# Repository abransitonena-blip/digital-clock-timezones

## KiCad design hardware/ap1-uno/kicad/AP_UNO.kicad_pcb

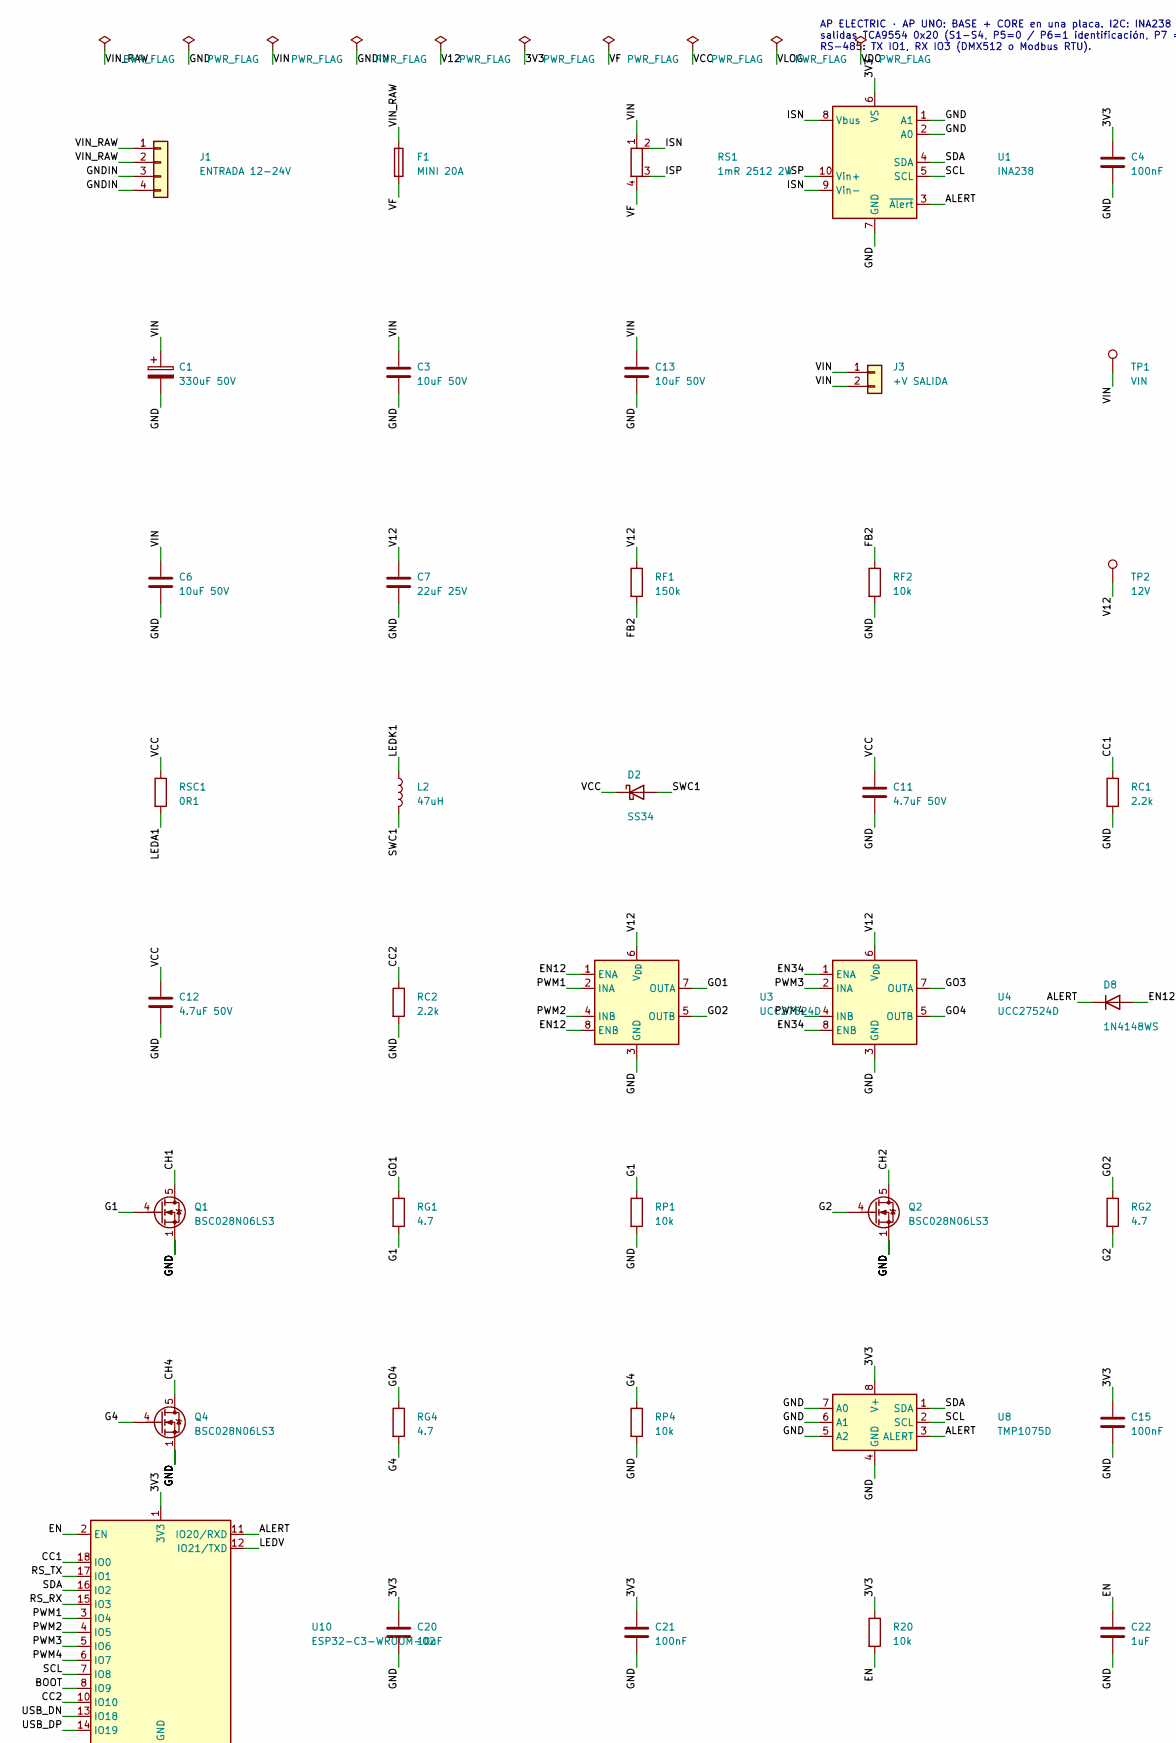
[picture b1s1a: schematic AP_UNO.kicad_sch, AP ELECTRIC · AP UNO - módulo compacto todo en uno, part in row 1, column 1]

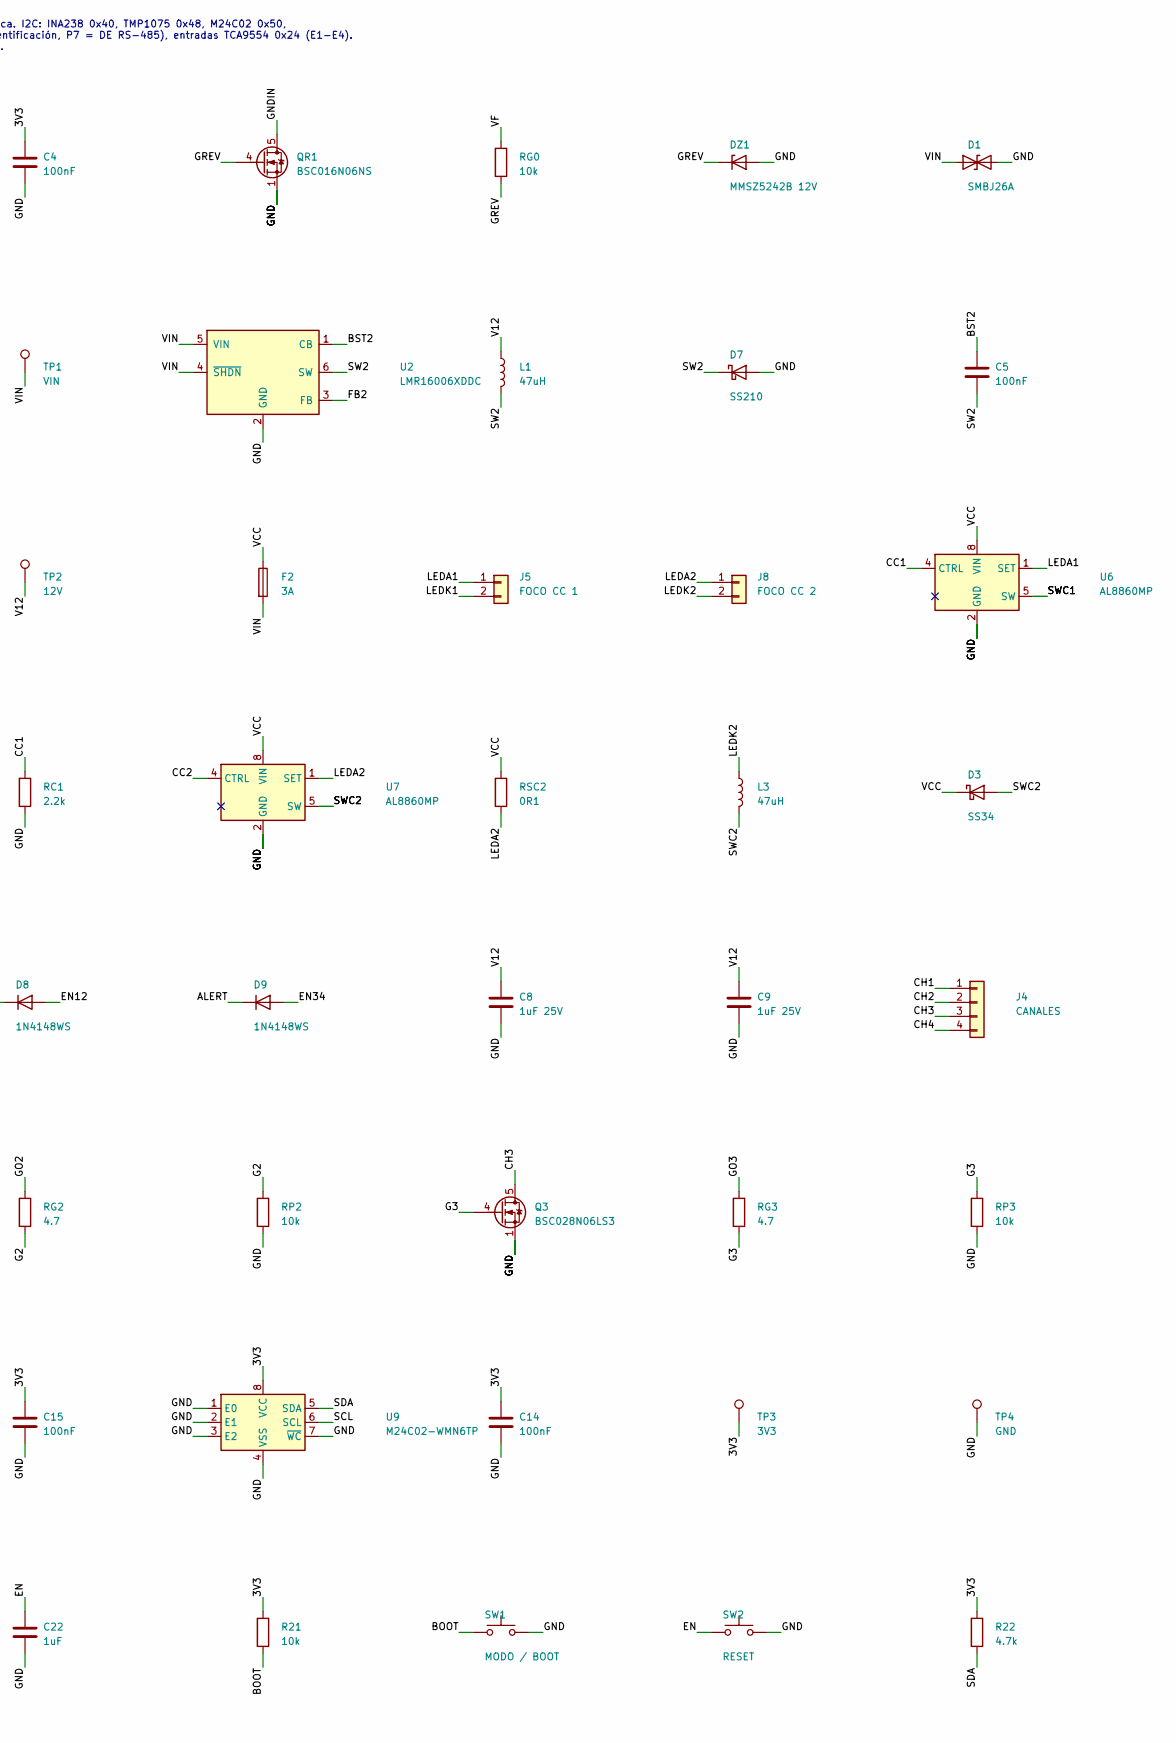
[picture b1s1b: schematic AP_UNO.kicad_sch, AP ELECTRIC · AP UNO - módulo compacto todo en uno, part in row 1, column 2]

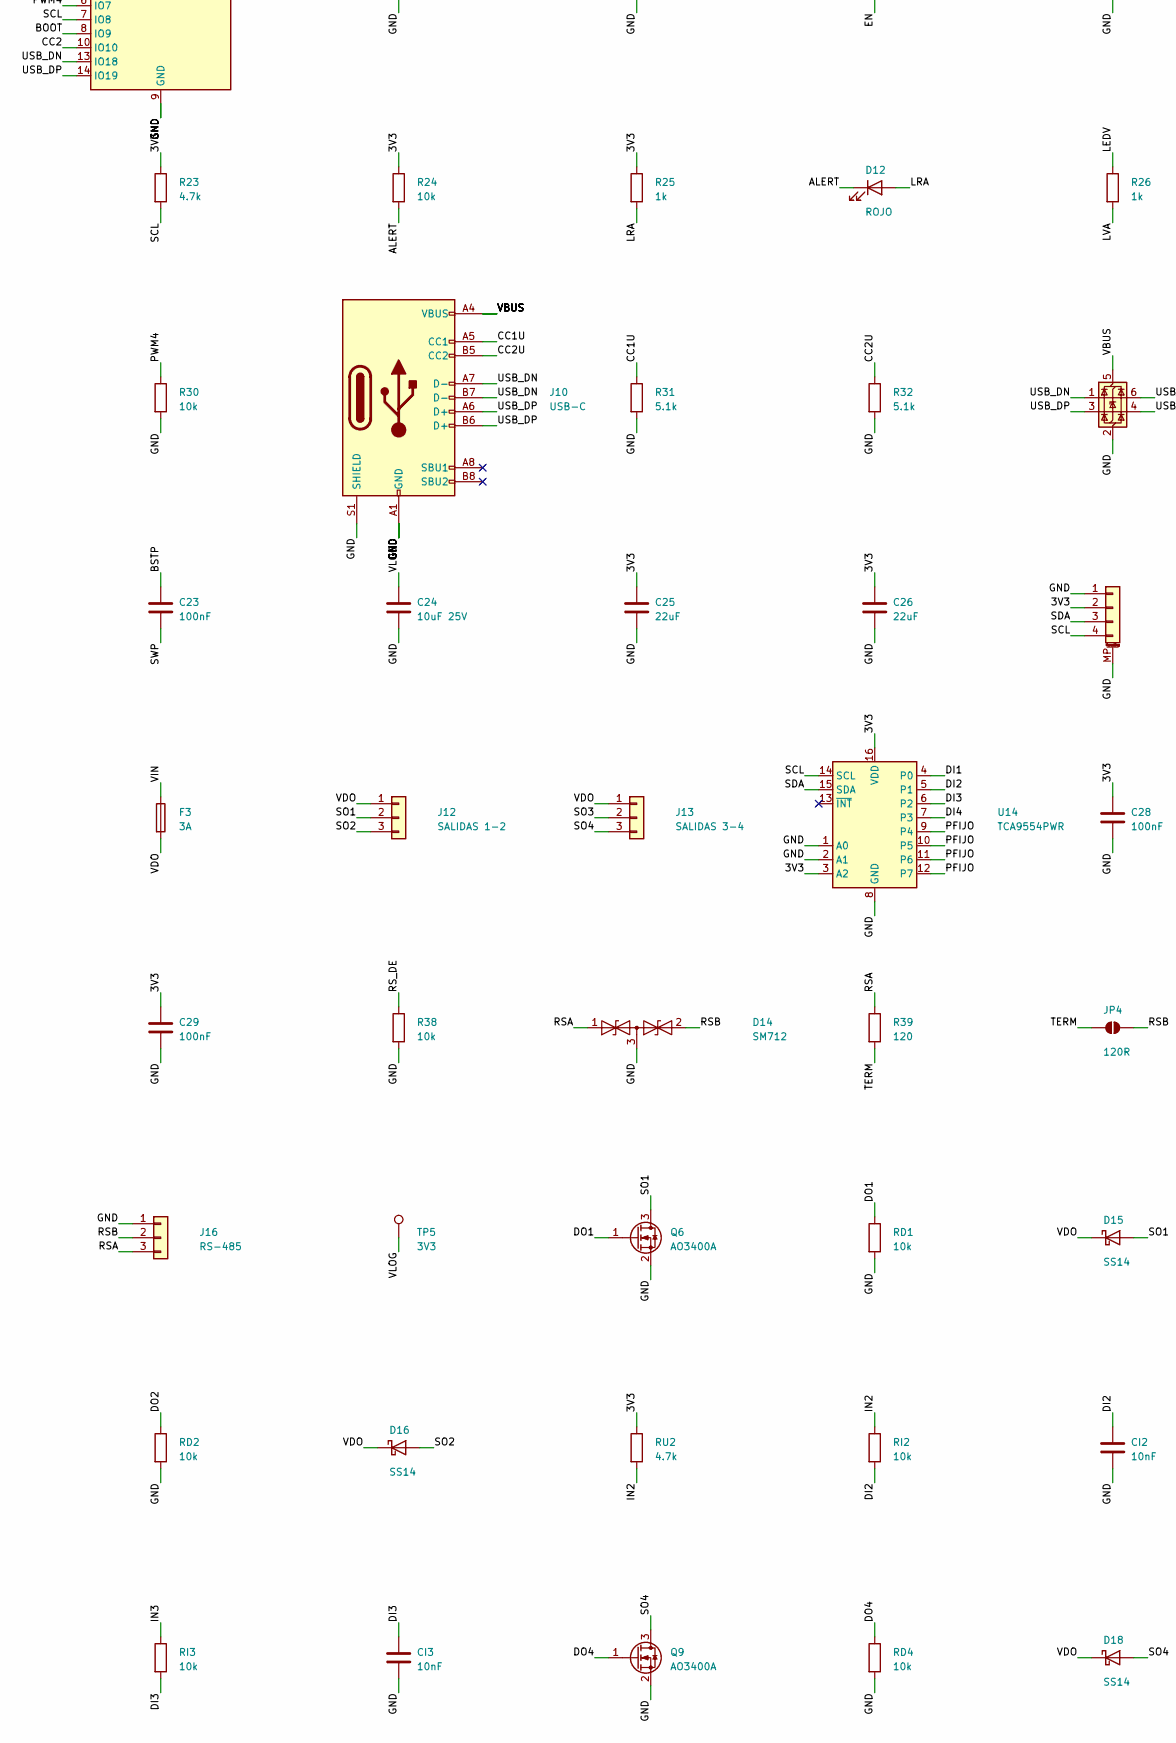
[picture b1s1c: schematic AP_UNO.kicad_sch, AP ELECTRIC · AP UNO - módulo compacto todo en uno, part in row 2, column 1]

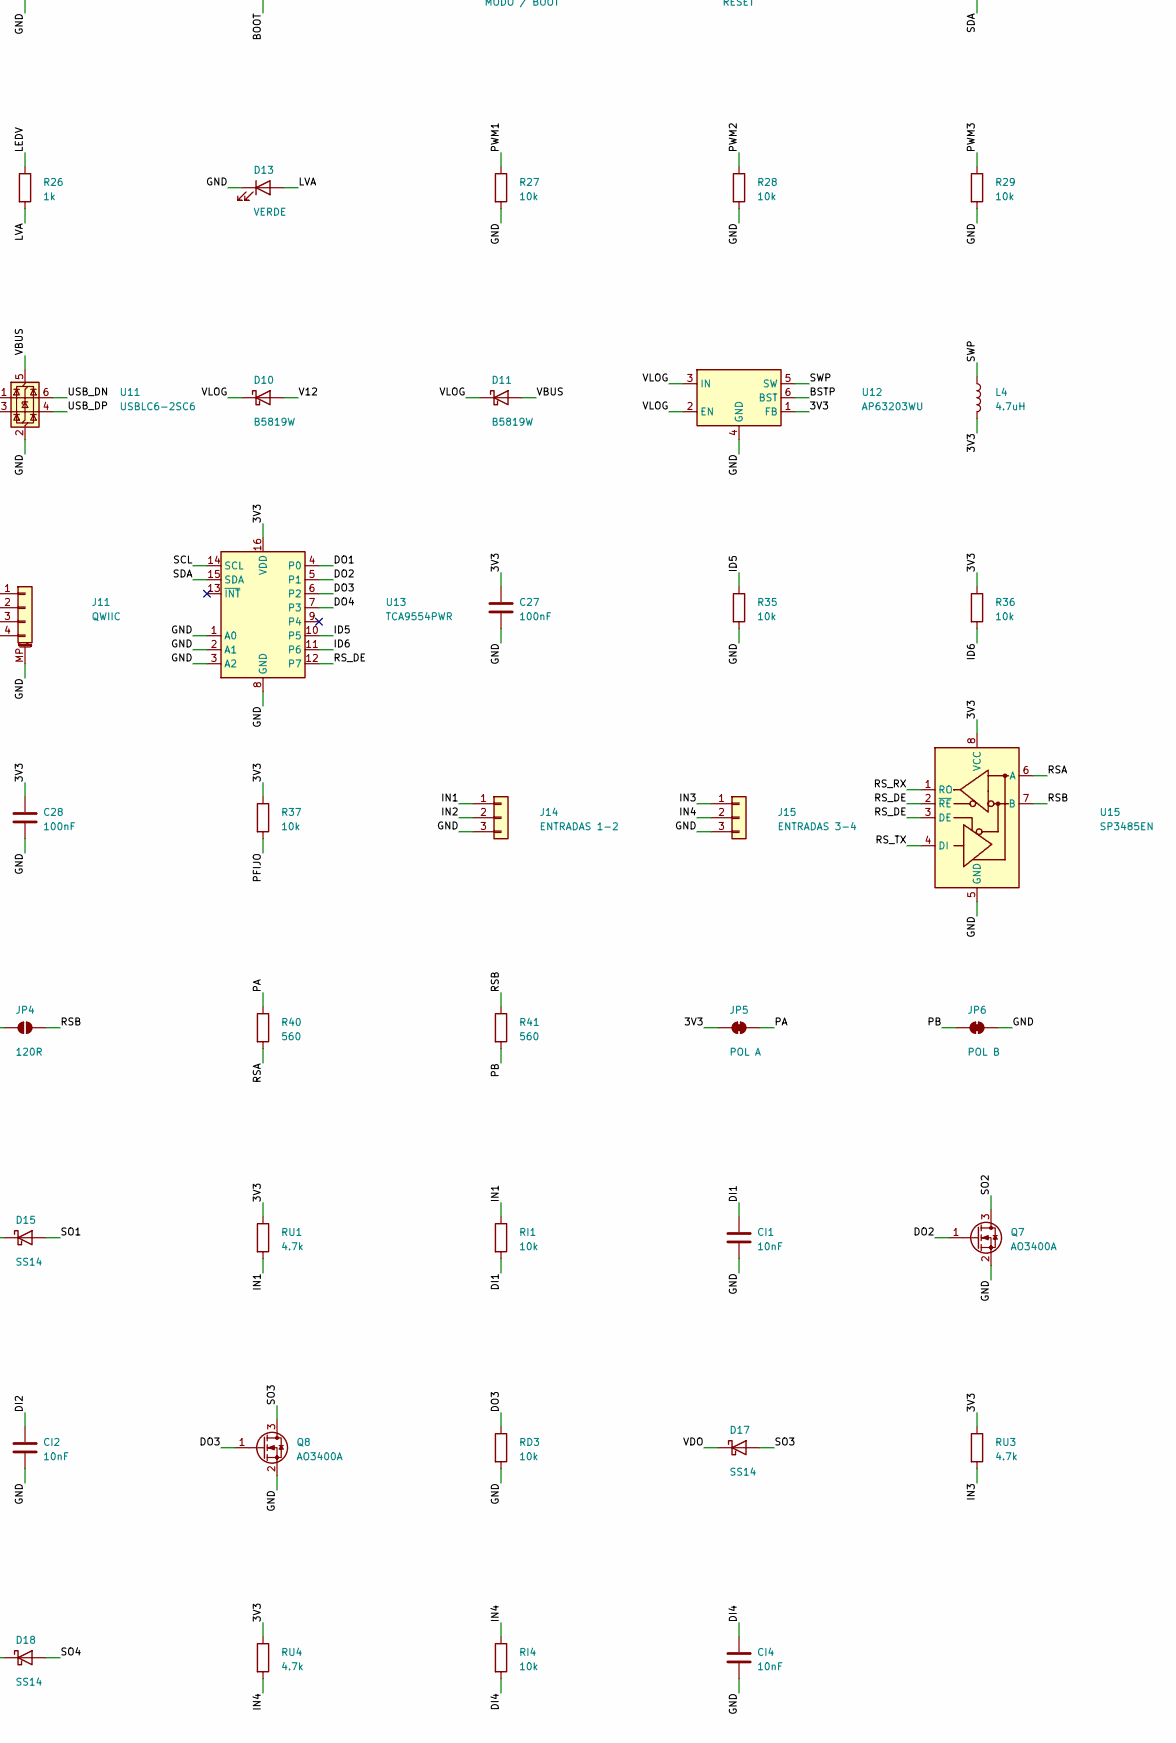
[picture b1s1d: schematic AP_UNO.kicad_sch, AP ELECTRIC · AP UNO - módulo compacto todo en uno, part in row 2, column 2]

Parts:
C1: 330uF 50V; CP_Elec_10x10.5
C3, C6, C13: 10uF 50V; C_1206_3216Metric
C4, C5, C14, C15, C21, C23, C27, C28, C29: 100nF; C_0603_1608Metric
C7: 22uF 25V; C_1206_3216Metric
C8, C9: 1uF 25V; C_0603_1608Metric
C11, C12: 4.7uF 50V; C_1206_3216Metric
C20: 10uF; C_0805_2012Metric
C22: 1uF; C_0603_1608Metric
C24: 10uF 25V; C_1206_3216Metric
C25, C26: 22uF; C_0805_2012Metric
CI1, CI2, CI3, CI4: 10nF; C_0603_1608Metric
D1: SMBJ26A; D_SMB
D2, D3: SS34; D_SMA
D7: SS210; D_SMA
D8, D9: 1N4148WS; D_SOD-323
D10, D11: B5819W; D_SOD-123
D12: ROJO; LED_0603_1608Metric
D13: VERDE; LED_0603_1608Metric
D14: SM712; SOT-23
D15, D16, D17, D18: SS14; D_SMA
DZ1: MMSZ5242B 12V; D_SOD-123
F1: MINI 20A; Fuseholder_Blade_Mini_Keystone_3568
F2, F3: 3A; Fuse_1206_3216Metric
J1: ENTRADA 12-24V; JST_VH_B4P-VH_1x04_P3.96mm_Vertical
J3: +V SALIDA; JST_VH_B2P-VH_1x02_P3.96mm_Vertical
J4: CANALES; JST_VH_B4P-VH_1x04_P3.96mm_Vertical
J5: FOCO CC 1; JST_XH_B2B-XH-A_1x02_P2.50mm_Vertical
J8: FOCO CC 2; JST_XH_B2B-XH-A_1x02_P2.50mm_Vertical
J10: USB-C; USB_C_Receptacle_HRO_TYPE-C-31-M-12
J11: QWIIC; JST_SH_SM04B-SRSS-TB_1x04-1MP_P1.00mm_Horizontal
J12: SALIDAS 1-2; JST_XH_B3B-XH-A_1x03_P2.50mm_Vertical
J13: SALIDAS 3-4; JST_XH_B3B-XH-A_1x03_P2.50mm_Vertical
J14: ENTRADAS 1-2; JST_XH_B3B-XH-A_1x03_P2.50mm_Vertical
J15: ENTRADAS 3-4; JST_XH_B3B-XH-A_1x03_P2.50mm_Vertical
J16: RS-485; JST_XH_B3B-XH-A_1x03_P2.50mm_Vertical
JP4: 120R; SolderJumper-2_P1.3mm_Open_RoundedPad1.0x1.5mm
JP5: POL A; SolderJumper-2_P1.3mm_Bridged_RoundedPad1.0x1.5mm
JP6: POL B; SolderJumper-2_P1.3mm_Bridged_RoundedPad1.0x1.5mm
L1: 47uH; L_Changjiang_FNR4030S
L2, L3: 47uH; L_Changjiang_FNR6045S
L4: 4.7uH; L_Changjiang_FNR4030S
Q1, Q2, Q3, Q4: BSC028N06LS3; TDSON-8-1
Q6, Q7, Q8, Q9: AO3400A; SOT-23
QR1: BSC016N06NS; TDSON-8-1
R20, R21, R24, R27, R28, R29, R30, R35, R36, R37, R38: 10k; R_0603_1608Metric
R22, R23: 4.7k; R_0603_1608Metric
R25, R26: 1k; R_0603_1608Metric
R31, R32: 5.1k; R_0603_1608Metric
R39: 120; R_1206_3216Metric
R40, R41: 560; R_0603_1608Metric
RC1, RC2: 2.2k; R_0603_1608Metric
RD1, RD2, RD3, RD4: 10k; R_0603_1608Metric
RF1: 150k; R_0603_1608Metric
RF2: 10k; R_0603_1608Metric
RG0: 10k; R_0603_1608Metric
RG1, RG2, RG3, RG4: 4.7; R_0603_1608Metric
RI1, RI2, RI3, RI4: 10k; R_0603_1608Metric
RP1, RP2, RP3, RP4: 10k; R_0603_1608Metric
RS1: 1mR 2512 2W; R_2512_Kelvin_NetTie
RSC1, RSC2: 0R1; R_1206_3216Metric
RU1, RU2, RU3, RU4: 4.7k; R_0603_1608Metric
SW1: MODO / BOOT; SW_Push_1P1T_XKB_TS-1187A
SW2: RESET; SW_Push_1P1T_XKB_TS-1187A
TP1: VIN; TestPoint_Pad_D1.5mm
TP2: 12V; TestPoint_Pad_D1.5mm
TP3, TP5: 3V3; TestPoint_Pad_D1.5mm
TP4: GND; TestPoint_Pad_D1.5mm
U1: INA238; VSSOP-10_3x3mm_P0.5mm
U2: LMR16006XDDC; SOT-23-6
U3, U4: UCC27524D; SOIC-8_3.9x4.9mm_P1.27mm
U6, U7: AL8860MP; MSOP-8-1EP_3x3mm_P0.65mm_EP1.5x1.8mm
U8: TMP1075D; SOIC-8_3.9x4.9mm_P1.27mm
U9: M24C02-WMN6TP; SOIC-8_3.9x4.9mm_P1.27mm
U10: ESP32-C3-WROOM-02; ESP32-C3-WROOM-02_JLC
U11: USBLC6-2SC6; SOT-23-6
U12: AP63203WU; TSOT-23-6
U13, U14: TCA9554PWR; TSSOP-16_4.4x5mm_P0.65mm
U15: SP3485EN; SOIC-8_3.9x4.9mm_P1.27mm

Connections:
/3V3: C4.1, C14.1, C15.1, C20.1, C21.1, C25.1, C26.1, C27.1, C28.1, C29.1, J11.2, JP5.1 (A), L4.2, R20.1, R21.1, R22.1, R23.1, R24.1, R25.1, R36.1, R37.1, RU1.1, RU2.1, RU3.1, RU4.1, TP3.1, U1.6 (VS), U8.8 (V+), U9.8 (VCC), U10.1 (3V3), U12.1 (FB), U13.16 (VDD), U14.3 (A2), U14.16 (VDD), U15.8 (VCC)
/ALERT: D8.1 (K), D9.1 (K), D12.1 (K), R24.2, U1.3 (~Alert), U8.3 (ALERT), U10.11 (IO20/RXD)
/BOOT: R21.2, SW1.1, U10.8 (IO9)
/BST2: C5.1, U2.1 (CB)
/BSTP: C23.1, U12.6 (BST)
/CC1: RC1.1, U6.4 (CTRL), U10.18 (IO0)
/CC1U: J10.A5 (CC1), R31.1
/CC2: RC2.1, U7.4 (CTRL), U10.10 (IO10)
/CC2U: J10.B5 (CC2), R32.1
/CH1: J4.1, Q1.5 (D)
/CH2: J4.2, Q2.5 (D)
/CH3: J4.3, Q3.5 (D)
/CH4: J4.4, Q4.5 (D)
/DI1: CI1.1, RI1.2, U14.4 (P0)
/DI2: CI2.1, RI2.2, U14.5 (P1)
/DI3: CI3.1, RI3.2, U14.6 (P2)
/DI4: CI4.1, RI4.2, U14.7 (P3)
/DO1: Q6.1 (G), RD1.1, U13.4 (P0)
/DO2: Q7.1 (G), RD2.1, U13.5 (P1)
/DO3: Q8.1 (G), RD3.1, U13.6 (P2)
/DO4: Q9.1 (G), RD4.1, U13.7 (P3)
/EN: C22.1, R20.2, SW2.1, U10.2 (EN)
/EN12: D8.2 (A), U3.1 (ENA), U3.8 (ENB)
/EN34: D9.2 (A), U4.1 (ENA), U4.8 (ENB)
/FB2: RF1.2, RF2.1, U2.3 (FB)
/G1: Q1.4 (G), RG1.2, RP1.1
/G2: Q2.4 (G), RG2.2, RP2.1
/G3: Q3.4 (G), RG3.2, RP3.1
/G4: Q4.4 (G), RG4.2, RP4.1
/GND: C1.2, C3.2, C4.2, C6.2, C7.2, C8.2, C9.2, C11.2, C12.2, C13.2, C14.2, C15.2, C20.2, C21.2, C22.2, C24.2, C25.2, C26.2, C27.2, C28.2, C29.2, CI1.2, CI2.2, CI3.2, CI4.2, D1.2 (A2), D7.2 (A), D13.1 (K), D14.3 (common), DZ1.2 (A), J10.A1 (GND), J10.A12 (GND), J10.B1 (GND), J10.B12 (GND), J10.S1 (SHIELD), J11.1, J11.MP (MountPin), J14.3, J15.3, J16.1, JP6.2 (B), Q1.1 (S), Q1.2 (S), Q1.3 (S), Q2.1 (S), Q2.2 (S), Q2.3 (S), Q3.1 (S), Q3.2 (S), Q3.3 (S), Q4.1 (S), Q4.2 (S), Q4.3 (S), Q6.2 (S), Q7.2 (S), Q8.2 (S), Q9.2 (S), QR1.1 (S), QR1.2 (S), QR1.3 (S), R27.2, R28.2, R29.2, R30.2, R31.2, R32.2, R35.2, R38.2, RC1.2, RC2.2, RD1.2, RD2.2, RD3.2, RD4.2, RF2.2, RP1.2, RP2.2, RP3.2, RP4.2, SW1.2, SW2.2, TP4.1, U1.1 (A1), U1.2 (A0), U1.7 (GND), U2.2 (GND), U3.3 (GND), U4.3 (GND), U6.2 (GND), U6.3 (GND), U6.9 (GND), U7.2 (GND), U7.3 (GND), U7.9 (GND), U8.4 (GND), U8.5 (A2), U8.6 (A1), U8.7 (A0), U9.1 (E0), U9.2 (E1), U9.3 (E2), U9.4 (VSS), U9.7 (~WC), U10.9 (GND), U10.19 (GND), U11.2 (GND), U12.4 (GND), U13.1 (A0), U13.2 (A1), U13.3 (A2), U13.8 (GND), U14.1 (A0), U14.2 (A1), U14.8 (GND), U15.5 (GND)
/GNDIN: J1.3, J1.4, QR1.5 (D)
/GO1: RG1.1, U3.7 (OUTA)
/GO2: RG2.1, U3.5 (OUTB)
/GO3: RG3.1, U4.7 (OUTA)
/GO4: RG4.1, U4.5 (OUTB)
/GREV: DZ1.1 (K), QR1.4 (G), RG0.2
/ID5: R35.1, U13.10 (P5)
/ID6: R36.2, U13.11 (P6)
/IN1: J14.1, RI1.1, RU1.2
/IN2: J14.2, RI2.1, RU2.2
/IN3: J15.1, RI3.1, RU3.2
/IN4: J15.2, RI4.1, RU4.2
/ISN: RS1.2, U1.8 (Vbus), U1.9 (Vin-)
/ISP: RS1.3, U1.10 (Vin+)
/LEDA1: J5.1, RSC1.2, U6.1 (SET)
/LEDA2: J8.1, RSC2.2, U7.1 (SET)
/LEDK1: J5.2, L2.1
/LEDK2: J8.2, L3.1
/LEDV: R26.1, U10.12 (IO21/TXD)
/LRA: D12.2 (A), R25.2
/LVA: D13.2 (A), R26.2
/PA: JP5.2 (B), R40.1
/PB: JP6.1 (A), R41.2
/PFIJO: R37.2, U14.9 (P4), U14.10 (P5), U14.11 (P6), U14.12 (P7)
/PWM1: R27.1, U3.2 (INA), U10.3 (IO4)
/PWM2: R28.1, U3.4 (INB), U10.4 (IO5)
/PWM3: R29.1, U4.2 (INA), U10.5 (IO6)
/PWM4: R30.1, U4.4 (INB), U10.6 (IO7)
/RSA: D14.1 (A1), J16.3, R39.1, R40.2, U15.6 (A)
/RSB: D14.2 (A2), J16.2, JP4.2 (B), R41.1, U15.7 (B)
/RS_DE: R38.1, U13.12 (P7), U15.2 (~RE), U15.3 (DE)
/RS_RX: U10.15 (IO3), U15.1 (RO)
/RS_TX: U10.17 (IO1), U15.4 (DI)
/SCL: J11.4, R23.2, U1.5 (SCL), U8.2 (SCL), U9.6 (SCL), U10.7 (IO8), U13.14 (SCL), U14.14 (SCL)
/SDA: J11.3, R22.2, U1.4 (SDA), U8.1 (SDA), U9.5 (SDA), U10.16 (IO2), U13.15 (SDA), U14.15 (SDA)
/SO1: D15.2 (A), J12.2, Q6.3 (D)
/SO2: D16.2 (A), J12.3, Q7.3 (D)
/SO3: D17.2 (A), J13.2, Q8.3 (D)
/SO4: D18.2 (A), J13.3, Q9.3 (D)
/SW2: C5.2, D7.1 (K), L1.2, U2.6 (SW)
/SWC1: D2.2 (A), L2.2, U6.5 (SW), U6.6 (SW)
/SWC2: D3.2 (A), L3.2, U7.5 (SW), U7.6 (SW)
/SWP: C23.2, L4.1, U12.5 (SW)
/TERM: JP4.1 (A), R39.2
/USB_DN: J10.A7 (D-), J10.B7 (D-), U10.13 (IO18), U11.1 (I/O1), U11.6 (I/O1)
/USB_DP: J10.A6 (D+), J10.B6 (D+), U10.14 (IO19), U11.3 (I/O2), U11.4 (I/O2)
/V12: C7.1, C8.1, C9.1, D10.2 (A), L1.1, RF1.1, TP2.1, U3.6 (V_{DD}), U4.6 (V_{DD})
/VBUS: D11.2 (A), J10.A4 (VBUS), J10.A9 (VBUS), J10.B4 (VBUS), J10.B9 (VBUS), U11.5 (VBUS)
/VCC: C11.1, C12.1, D2.1 (K), D3.1 (K), F2.1, RSC1.1, RSC2.1, U6.8 (VIN), U7.8 (VIN)
/VDO: D15.1 (K), D16.1 (K), D17.1 (K), D18.1 (K), F3.2, J12.1, J13.1
/VF: F1.2, RG0.1, RS1.4
/VIN: C1.1, C3.1, C6.1, C13.1, D1.1 (A1), F2.2, F3.1, J3.1, J3.2, RS1.1, TP1.1, U2.4 (~SHDN), U2.5 (VIN)
/VIN_RAW: F1.1, J1.1, J1.2
/VLOG: C24.1, D10.1 (K), D11.1 (K), TP5.1, U12.2 (EN), U12.3 (IN)

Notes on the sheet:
AP ELECTRIC · AP UNO: BASE + CORE en una placa. I2C: INA238 0x40, TMP1075 0x48, M24C02 0x50, salidas TCA9554 0x20 (S1-S4, P5=0 / P6=1 identificación, P7 = DE RS-485), entradas TCA9554 0x24 (E1-E4). RS-485: TX IO1, RX IO3 (DMX512 o Modbus RTU).

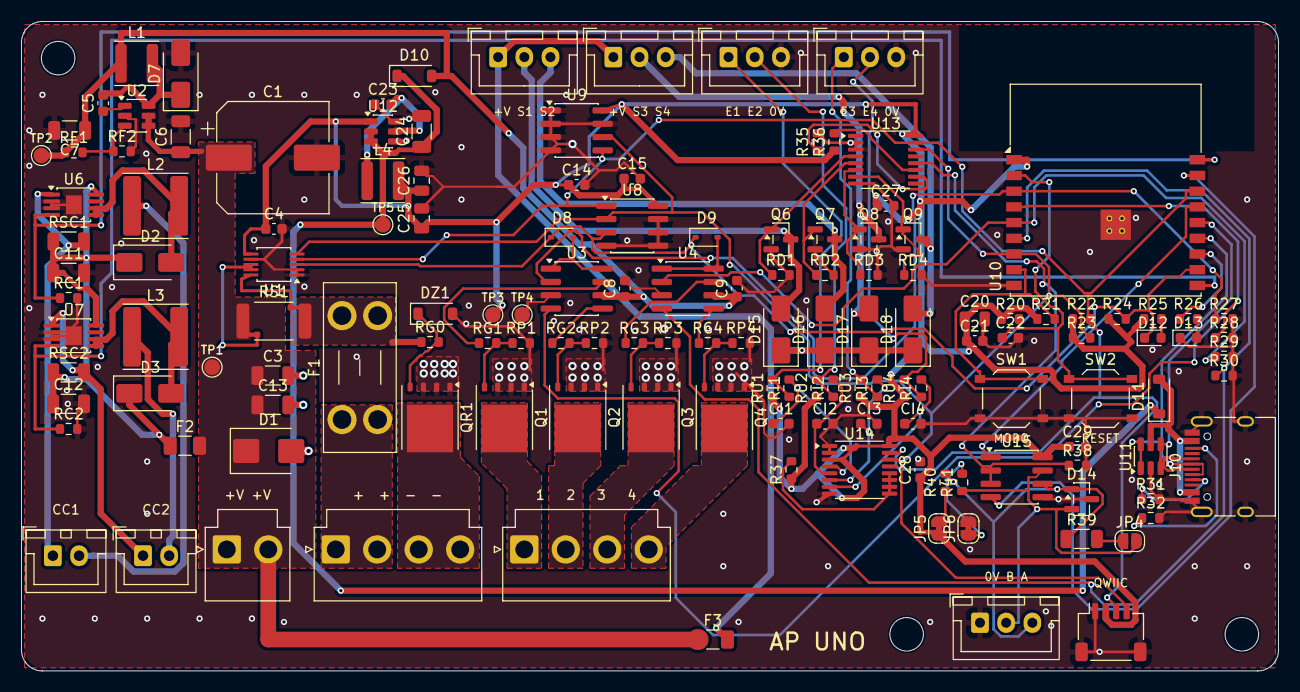
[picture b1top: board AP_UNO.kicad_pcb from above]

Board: 4 copper layers, 120.0 x 62.0 mm, 146 parts (0 on the bottom side), 84 nets.

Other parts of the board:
H1, H2, H3: MountingHole_3.2mm_M3

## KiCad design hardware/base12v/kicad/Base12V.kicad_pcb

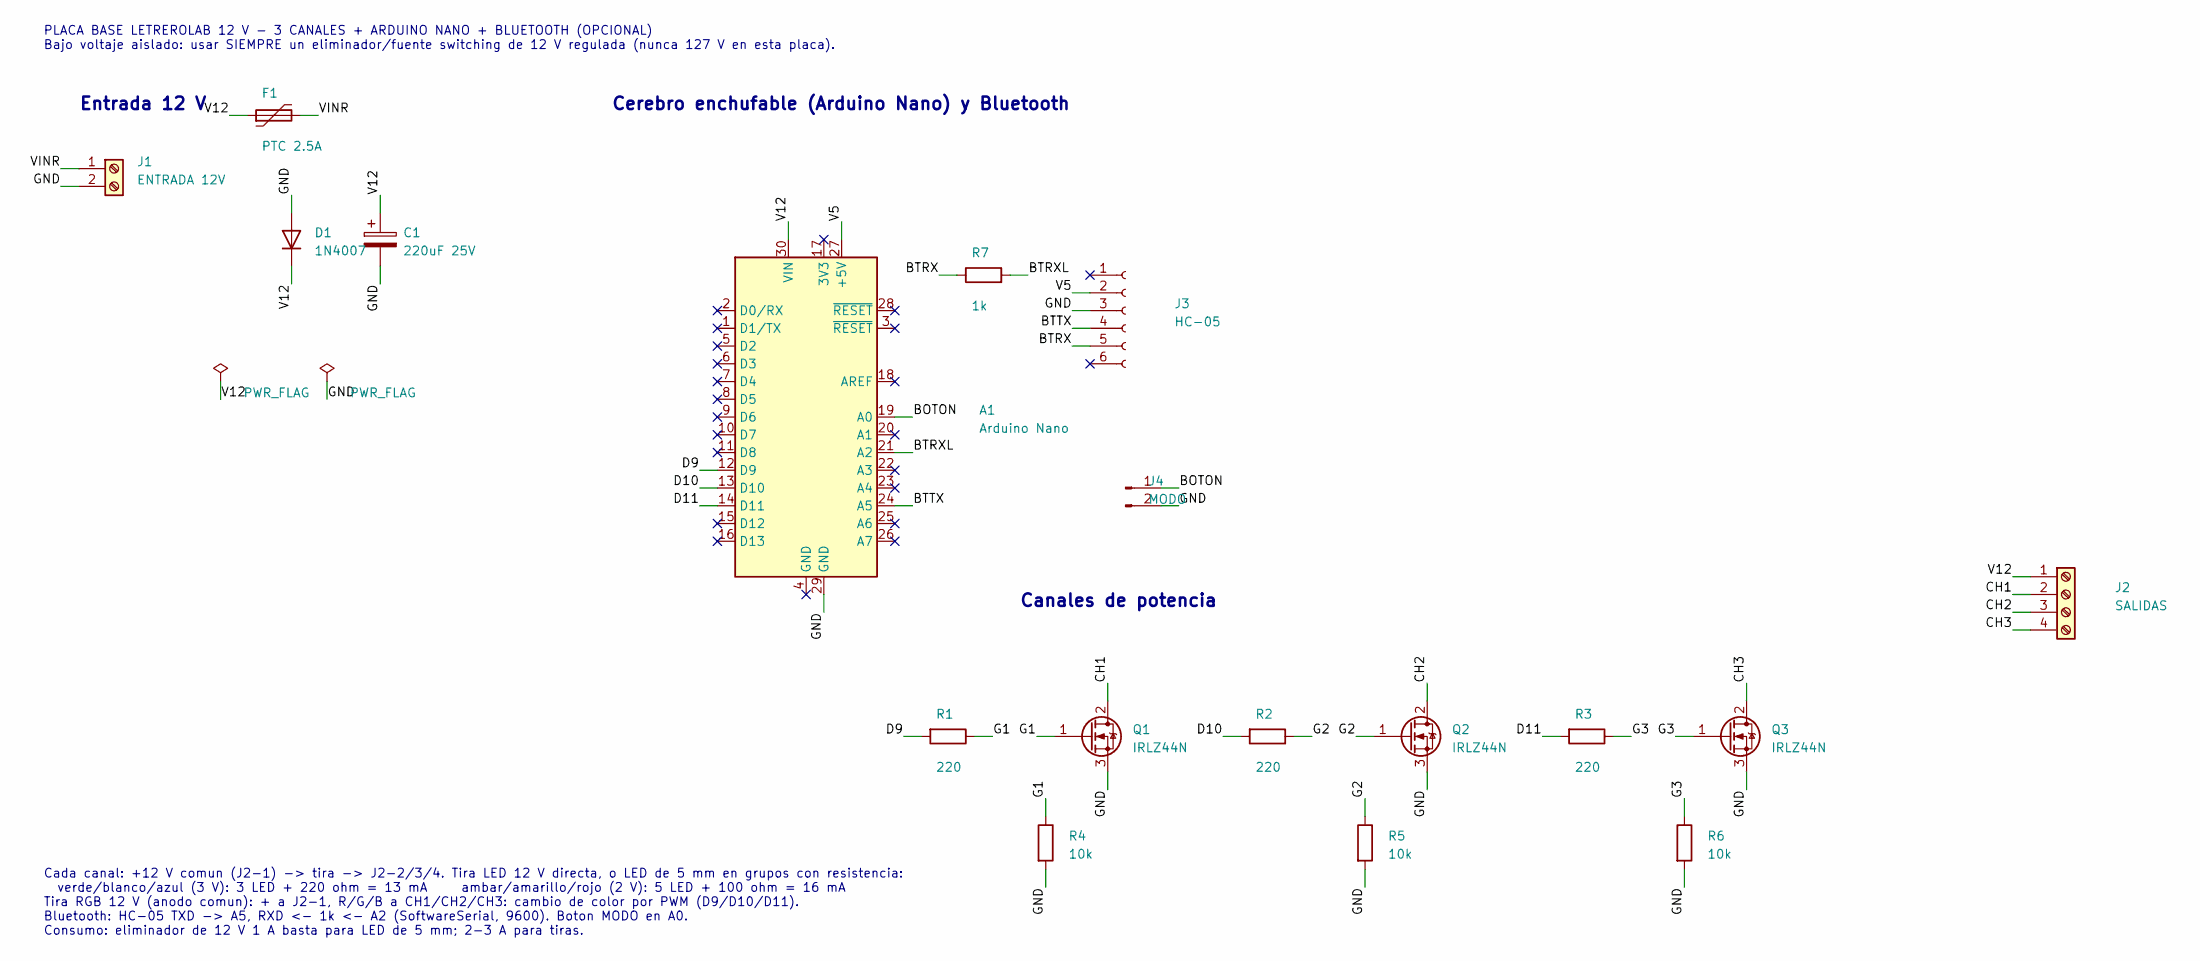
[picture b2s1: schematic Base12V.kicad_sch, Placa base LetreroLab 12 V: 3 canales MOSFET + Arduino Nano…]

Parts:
A1: Arduino Nano; Arduino_Nano_Zocalo
C1: 220uF 25V; CP_Radial_D8.0mm_P3.81mm
D1: 1N4007; D_DO-41_Vertical_P5.08mm
F1: PTC 2.5A; PTC_Radial_P5.08mm
J1: ENTRADA 12V; Clema_2P_P5.08mm
J2: SALIDAS; Clema_4P_P5.08mm
J3: HC-05; Zocalo_1x06_P2.54mm
J4: MODO; Cables_2P_P5.08mm
Q1, Q2, Q3: IRLZ44N; TO-220_MOSFET
R1, R2, R3: 220; R_Vertical_P5.08mm
R4, R5, R6: 10k; R_Vertical_P5.08mm
R7: 1k; R_Vertical_P5.08mm

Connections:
/BOTON: A1.19 (A0), J4.1
/BTRX: J3.5, R7.1
/BTRXL: A1.21 (A2), R7.2
/BTTX: A1.24 (A5), J3.4
/CH1: J2.2, Q1.2 (D)
/CH2: J2.3, Q2.2 (D)
/CH3: J2.4, Q3.2 (D)
/D9: A1.12 (D9), R1.2
/D10: A1.13 (D10), R2.2
/D11: A1.14 (D11), R3.2
/G1: Q1.1 (G), R1.1, R4.1
/G2: Q2.1 (G), R2.1, R5.1
/G3: Q3.1 (G), R3.1, R6.1
/GND: A1.29 (GND), C1.2, D1.2 (A), J1.2, J3.3, J4.2, Q1.3 (S), Q2.3 (S), Q3.3 (S), R4.2, R5.2, R6.2
/V5: A1.27 (+5V), J3.2
/V12: A1.30 (VIN), C1.1, D1.1 (K), F1.1, J2.1
/VINR: F1.2, J1.1

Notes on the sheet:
PLACA BASE LETREROLAB 12 V - 3 CANALES + ARDUINO NANO + BLUETOOTH (OPCIONAL) Bajo voltaje aislado: usar SIEMPRE un eliminador/fuente switching de 12 V regulada (nunca 127 V en esta placa).
Cada canal: +12 V comun (J2-1) -> tira -> J2-2/3/4. Tira LED 12 V directa, o LED de 5 mm en grupos con resistencia: verde/blanco/azul (3 V): 3 LED + 220 ohm = 13 mA ambar/amarillo/rojo (2 V): 5 LED + 100 ohm = 16 mA Tira RGB 12 V (anodo comun): + a J2-1, R/G/B a CH1/CH2/CH3: cambio de color por PWM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
Entrada 12 V
Cerebro enchufable (Arduino Nano) y Bluetooth
Canales de potencia

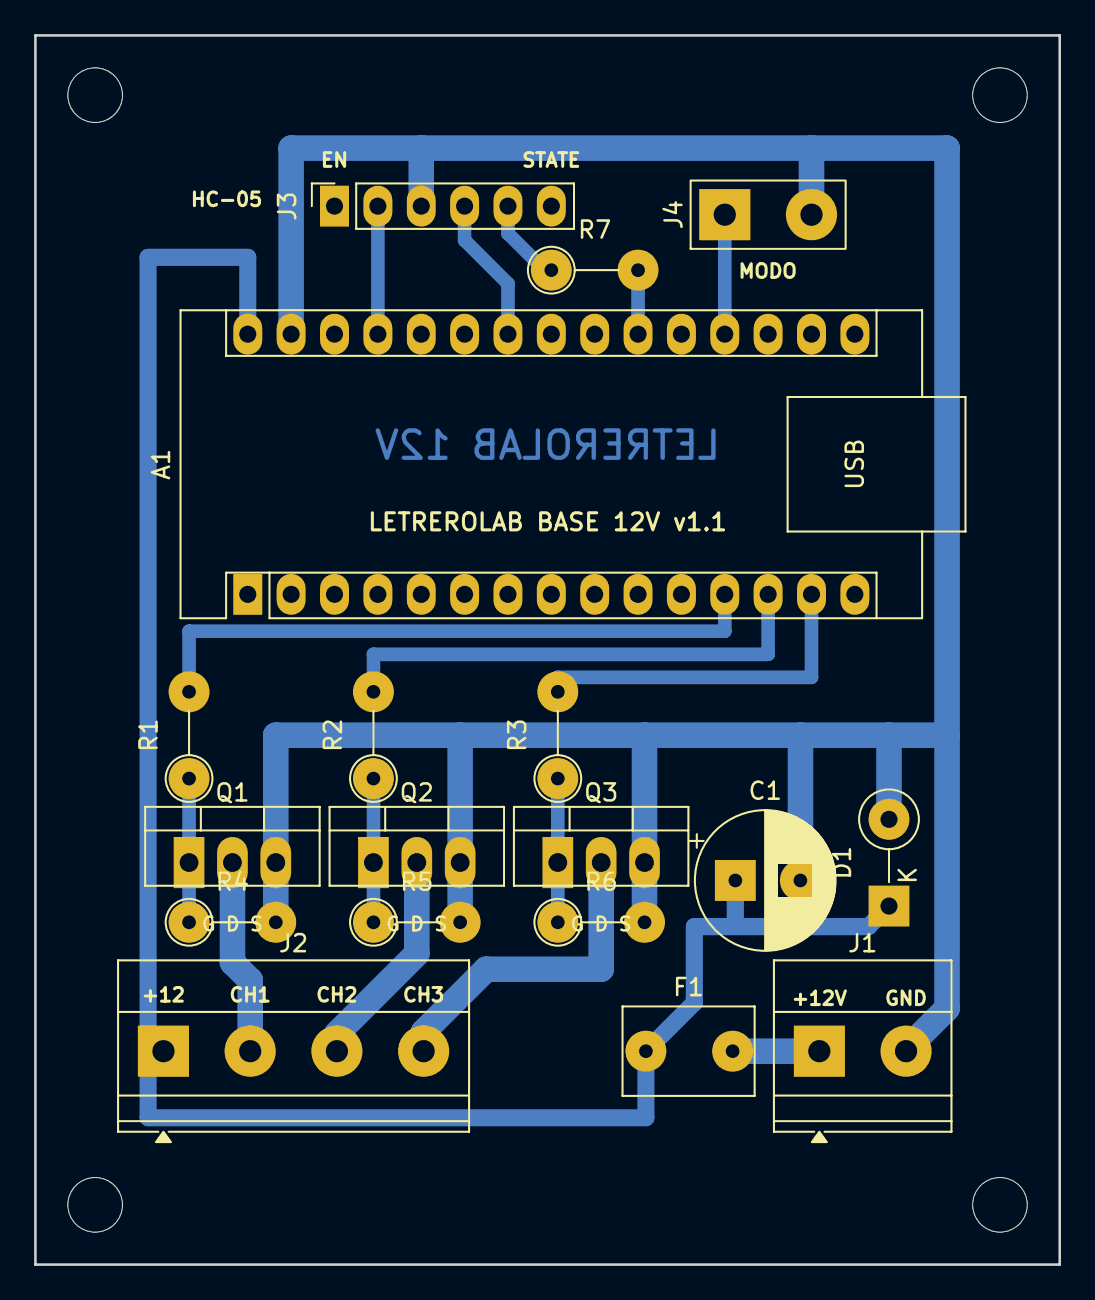
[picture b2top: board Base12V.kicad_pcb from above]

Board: 2 copper layers, 60.0 x 72.0 mm, 22 parts (0 on the bottom side), 17 nets.

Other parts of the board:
H1, H2, H3, H4: MountingHole_3.2mm_M3; Barreno_M3_3.2mm

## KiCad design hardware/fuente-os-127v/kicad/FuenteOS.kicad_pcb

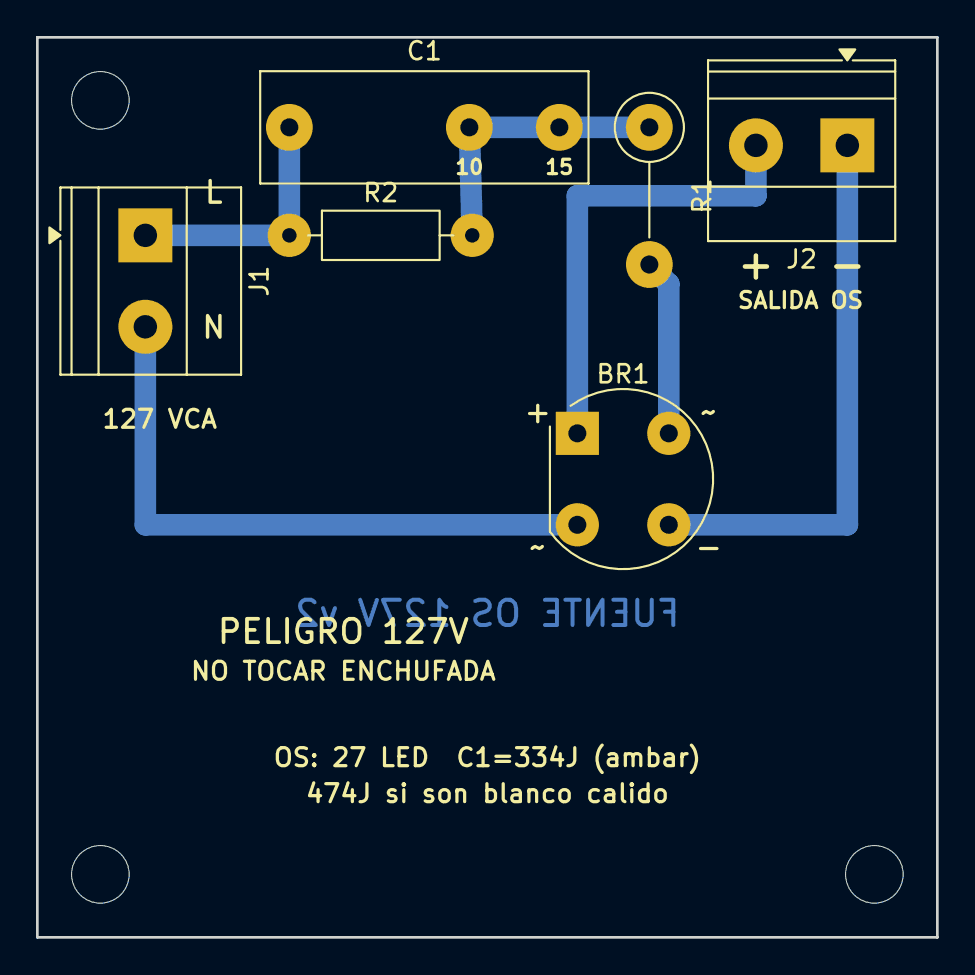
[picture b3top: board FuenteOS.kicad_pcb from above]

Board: 2 copper layers, 50.0 x 50.0 mm, 9 parts (0 on the bottom side), 6 nets.

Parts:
BR1: 2W10; Puente_2W10
C1: 334J 400V; C_Poliester_P10-15mm
H1, H2, H3: MountingHole_3.2mm_M3; Barreno_M3_3.2mm
J1: 127 VCA; Clema_2P_P5.08mm
J2: SALIDA OS; Clema_2P_P5.08mm
R1: 220R 1W fusible; R_1W_Vertical_P7.62mm
R2: 1M 1/2W; R_Axial_P10.16mm

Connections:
/AC: BR1.4, R1.2
/L: C1.1, J1.1, R2.1
/N: BR1.3, J1.2
/OS+: BR1.1, J2.2
/OS-: BR1.2, J2.1
/X: C1.2, R1.1, R2.2

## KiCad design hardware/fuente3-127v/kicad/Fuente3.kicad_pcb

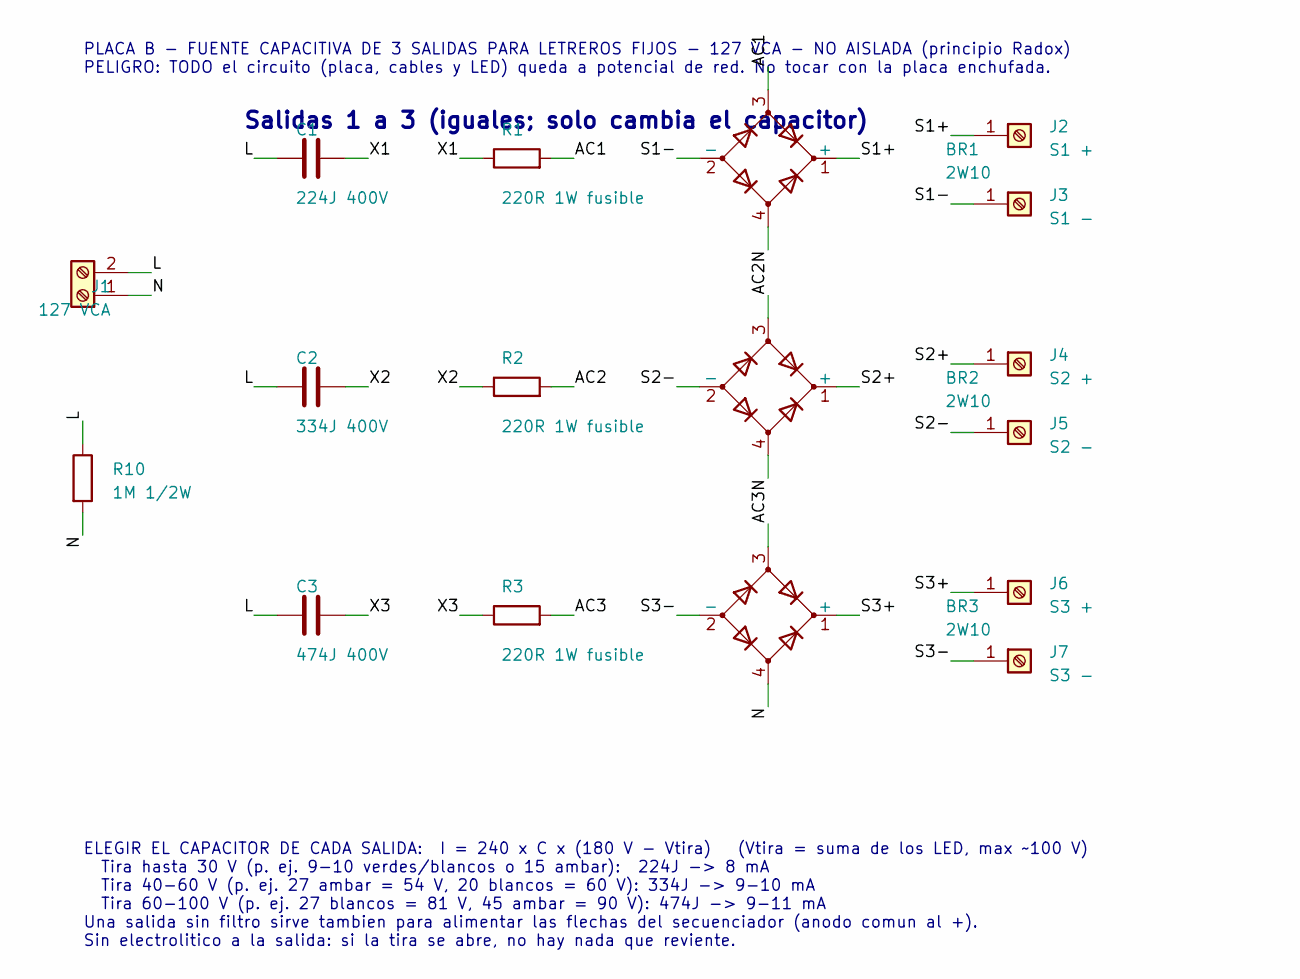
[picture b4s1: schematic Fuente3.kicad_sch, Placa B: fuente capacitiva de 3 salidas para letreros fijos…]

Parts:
BR1, BR2, BR3: 2W10; Puente_2W10
C1: 224J 400V; C_Poliester_P10-15mm
C2: 334J 400V; C_Poliester_P10-15mm
C3: 474J 400V; C_Poliester_P10-15mm
J1: 127 VCA; Clema_2P_P5.08mm
J2: S1 +; Cables_1P_P5.08mm
J3: S1 -; Cables_1P_P5.08mm
J4: S2 +; Cables_1P_P5.08mm
J5: S2 -; Cables_1P_P5.08mm
J6: S3 +; Cables_1P_P5.08mm
J7: S3 -; Cables_1P_P5.08mm
R1, R2, R3: 220R 1W fusible; R_1W_Vertical_P7.62mm
R10: 1M 1/2W; R_Vertical_P5.08mm

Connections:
/AC1: BR1.3, R1.2
/AC2: BR2.3, R2.2
/AC3: BR3.3, R3.2
/L: C1.1, C2.1, C3.1, J1.2, R10.1
/N: BR1.4, BR2.4, BR3.4, J1.1, R10.2
/S1+: BR1.1 (+), J2.1
/S1-: BR1.2 (-), J3.1
/S2+: BR2.1 (+), J4.1
/S2-: BR2.2 (-), J5.1
/S3+: BR3.1 (+), J6.1
/S3-: BR3.2 (-), J7.1
/X1: C1.2, R1.1
/X2: C2.2, R2.1
/X3: C3.2, R3.1

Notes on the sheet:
PLACA B - FUENTE CAPACITIVA DE 3 SALIDAS PARA LETREROS FIJOS - 127 VCA - NO AISLADA (principio Radox) PELIGRO: TODO el circuito (placa, cables y LED) queda a potencial de red. No tocar con la placa enchufada.
ELEGIR EL CAPACITOR DE CADA SALIDA: I = 240 x C x (180 V - Vtira) (Vtira = suma de los LED, max ~100 V) Tira hasta 30 V (p. ej. 9-10 verdes/blancos o 15 ambar): 224J -> 8 mA Tira 40-60 V (p. ej. 27 ambar = 54 V, 20 blancos = 60 V): 334J -> 9-10 mA Tira 60-100 V (p. ej. 27 blancos = 81 V, 45 ambar =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
Salidas 1 a 3 (iguales; solo cambia el capacitor)

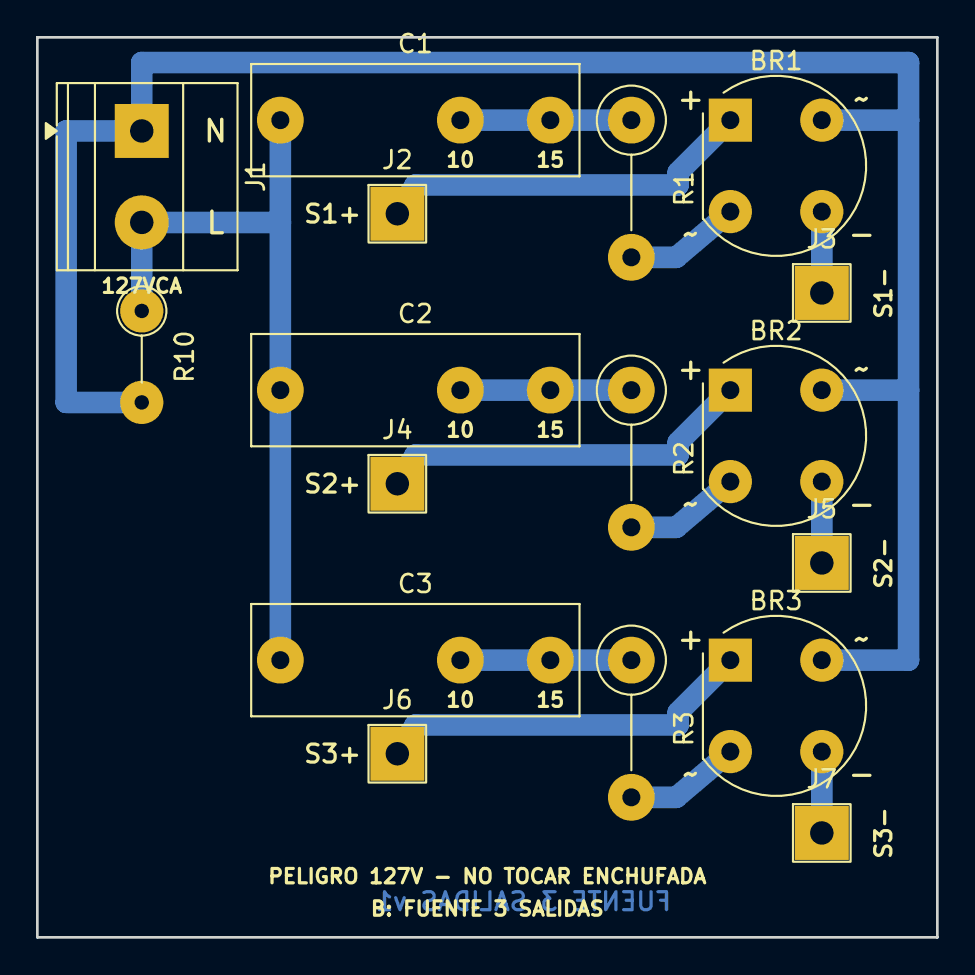
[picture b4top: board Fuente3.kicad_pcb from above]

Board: 2 copper layers, 50.0 x 50.0 mm, 17 parts (0 on the bottom side), 14 nets.
